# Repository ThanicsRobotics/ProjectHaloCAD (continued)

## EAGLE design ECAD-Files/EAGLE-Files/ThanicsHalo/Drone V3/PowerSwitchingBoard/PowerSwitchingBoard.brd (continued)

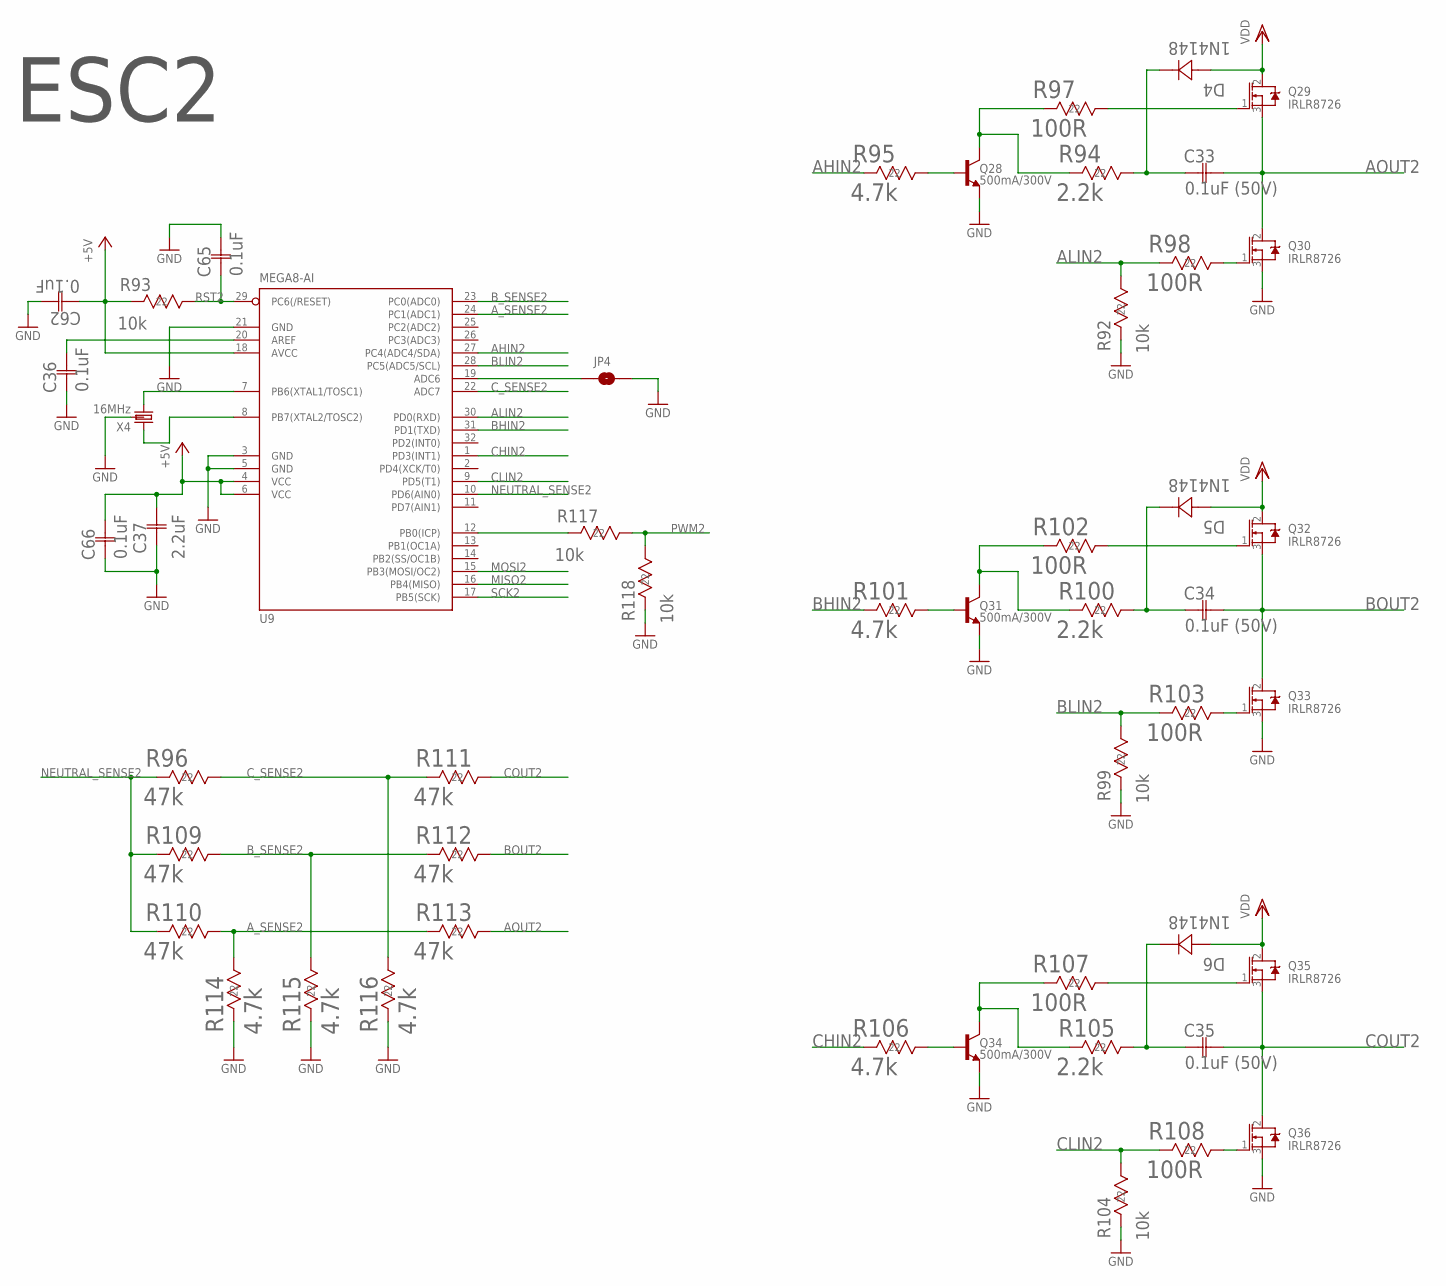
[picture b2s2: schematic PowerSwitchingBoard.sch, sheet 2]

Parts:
C33, C34, C35: 0.1uF (50V); 0402-M
C36, C62, C65, C66: 0.1uF; 0402-M
C37: 2.2uF; G-188-M
D4, D5, D6: 1N4148; SOD123-M
JP4: JUMPER-SMT_2_NO_NO-SILK; SMT-JUMPER_2_NO_NO-SILK
Q28, Q31, Q34: 500mA/300V; SOT23-3
Q29, Q30, Q32, Q33, Q35, Q36: IRLR8726; DPAK
R92, R93, R99, R104, R117, R118: 10k; RC0603N-M
R94, R100, R105: 2.2k; RC0603N-M
R95, R101, R106, R114, R115, R116: 4.7k; RC0603N-M
R96, R109, R110, R111, R112, R113: 47k; RC0603N-M
R97, R98, R102, R103, R107, R108: 100R; RC0603N-M
U9: MEGA8-AI; TQFP32-08
X4: 16MHz; 3-SMD

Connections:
+5V: C37.2 (22), C62.1, C66.2, R93.2 (22), U9.4 (VCC), U9.6 (VCC), U9.18 (AVCC); also elsewhere on the board
AHIN2: R95.2 (22), U9.27 (PC4(ADC4/SDA))
ALIN2: R92.1 (11), R98.2 (22), U9.30 (PD0(RXD))
AOUT2: C33.2, Q29.3 (S), Q30.2 (D), R113.1 (11)
A_SENSE2: R110.1 (11), R113.2 (22), R114.1 (11), U9.24 (PC1(ADC1))
BHIN2: R101.2 (22), U9.31 (PD1(TXD))
BLIN2: R99.1 (11), R103.2 (22), U9.28 (PC5(ADC5/SCL))
BOUT2: C34.2, Q32.3 (S), Q33.2 (D), R112.1 (11)
B_SENSE2: R109.1 (11), R112.2 (22), R115.1 (11), U9.23 (PC0(ADC0))
CHIN2: R106.2 (22), U9.1 (PD3(INT1))
CLIN2: R104.1 (11), R108.2 (22), U9.9 (PD5(T1))
COUT2: C35.2, Q35.3 (S), Q36.2 (D), R111.1 (11)
C_SENSE2: R96.1 (11), R111.2 (22), R116.1 (11), U9.22 (ADC7)
GND: C36.1, C37.1 (11), C62.2, C65.2, C66.1, JP4.2, Q28.2 (E), Q30.3 (S), Q31.2 (E), Q33.3 (S), Q34.2 (E), Q36.3 (S), R92.2 (22), R99.2 (22), R104.2 (22), R114.2 (22), R115.2 (22), R116.2 (22), R118.2 (22), U9.3 (GND), U9.5 (GND), U9.21 (GND), X4.2 (GND); also elsewhere on the board
MISO2: U9.16 (PB4(MISO)); also elsewhere on the board
MOSI2: U9.15 (PB3(MOSI/OC2)); also elsewhere on the board
unnamed: Q28.1 (B), R95.1 (11)
unnamed: Q29.1 (G), R97.1 (11)
unnamed: Q28.3 (C), R94.2 (22), R97.2 (22)
unnamed: C33.1, D4.C (12), R94.1 (11)
unnamed: Q30.1 (G), R98.1 (11)
unnamed: Q31.1 (B), R101.1 (11)
unnamed: Q32.1 (G), R102.1 (11)
unnamed: Q31.3 (C), R100.2 (22), R102.2 (22)
unnamed: C34.1, D5.C (12), R100.1 (11)
unnamed: Q33.1 (G), R103.1 (11)
unnamed: Q34.1 (B), R106.1 (11)
unnamed: Q35.1 (G), R107.1 (11)
unnamed: Q34.3 (C), R105.2 (22), R107.2 (22)
unnamed: C35.1, D6.C (12), R105.1 (11)
unnamed: Q36.1 (G), R108.1 (11)
unnamed: R117.2 (22), U9.12 (PB0(ICP))
unnamed: JP4.1, U9.19 (ADC6)
unnamed: C36.2, U9.20 (AREF)
unnamed: U9.7 (PB6(XTAL1/TOSC1)), X4.3 (2)
unnamed: U9.8 (PB7(XTAL2/TOSC2)), X4.1
NEUTRAL_SENSE2: R96.2 (22), R109.2 (22), R110.2 (22), U9.10 (PD6(AIN0))
PWM2: R117.1 (11), R118.1 (11); also elsewhere on the board
RST2: C65.1, R93.1 (11), U9.29 (PC6(/RESET)); also elsewhere on the board
SCK2: U9.17 (PB5(SCK)); also elsewhere on the board
VDD: D4.A (21), D5.A (21), D6.A (21), Q29.2 (D), Q32.2 (D), Q35.2 (D); also elsewhere on the board

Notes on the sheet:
ESC2

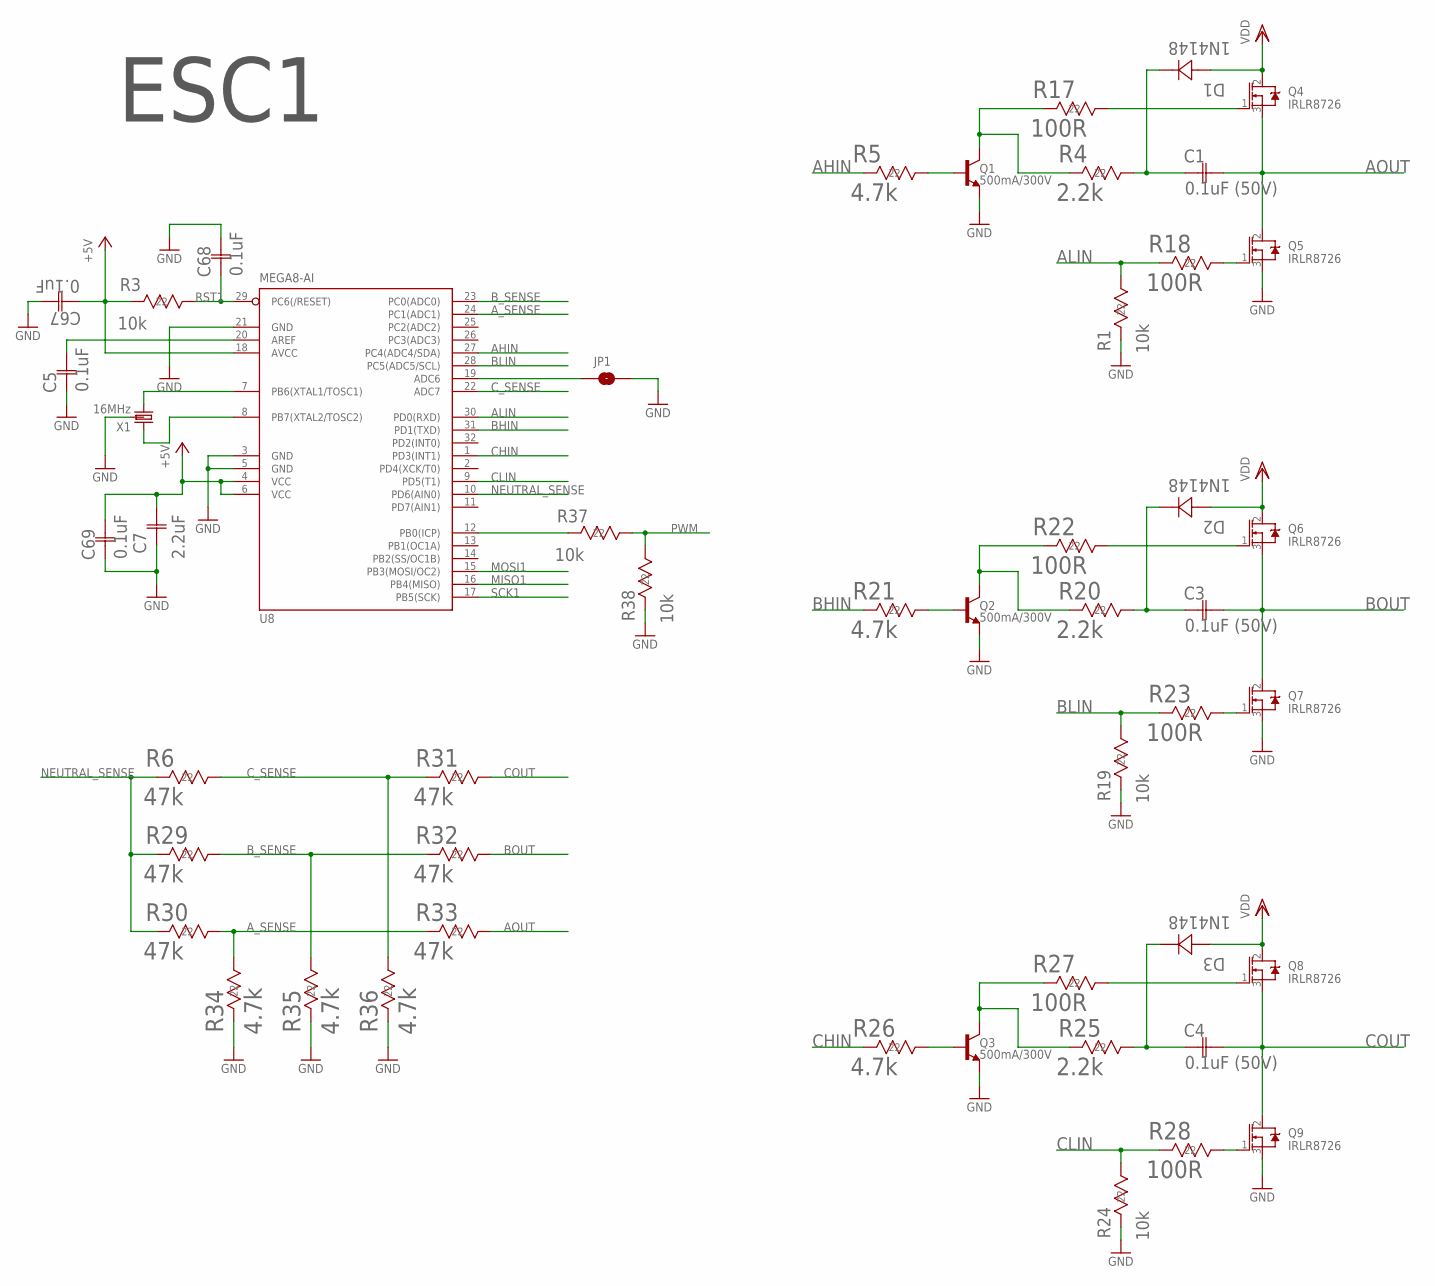
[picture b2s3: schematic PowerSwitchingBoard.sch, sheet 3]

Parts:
C1, C3, C4: 0.1uF (50V); 0402-M
C5, C67, C68, C69: 0.1uF; 0402-M
C7: 2.2uF; G-188-M
D1, D2, D3: 1N4148; SOD123-M
JP1: JUMPER-SMT_2_NO_NO-SILK; SMT-JUMPER_2_NO_NO-SILK
Q1, Q2, Q3: 500mA/300V; SOT23-3
Q4, Q5, Q6, Q7, Q8, Q9: IRLR8726; DPAK
R1, R3, R19, R24, R37, R38: 10k; RC0603N-M
R4, R20, R25: 2.2k; RC0603N-M
R5, R21, R26, R34, R35, R36: 4.7k; RC0603N-M
R6, R29, R30, R31, R32, R33: 47k; RC0603N-M
R17, R18, R22, R23, R27, R28: 100R; RC0603N-M
U8: MEGA8-AI; TQFP32-08
X1: 16MHz; 3-SMD

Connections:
+5V: C7.2 (22), C67.1, C69.2, R3.2 (22), U8.4 (VCC), U8.6 (VCC), U8.18 (AVCC); also elsewhere on the board
AHIN: R5.2 (22), U8.27 (PC4(ADC4/SDA))
ALIN: R1.1 (11), R18.2 (22), U8.30 (PD0(RXD))
AOUT: C1.2, Q4.3 (S), Q5.2 (D), R33.1 (11)
A_SENSE: R30.1 (11), R33.2 (22), R34.1 (11), U8.24 (PC1(ADC1))
BHIN: R21.2 (22), U8.31 (PD1(TXD))
BLIN: R19.1 (11), R23.2 (22), U8.28 (PC5(ADC5/SCL))
BOUT: C3.2, Q6.3 (S), Q7.2 (D), R32.1 (11)
B_SENSE: R29.1 (11), R32.2 (22), R35.1 (11), U8.23 (PC0(ADC0))
CHIN: R26.2 (22), U8.1 (PD3(INT1))
CLIN: R24.1 (11), R28.2 (22), U8.9 (PD5(T1))
COUT: C4.2, Q8.3 (S), Q9.2 (D), R31.1 (11)
C_SENSE: R6.1 (11), R31.2 (22), R36.1 (11), U8.22 (ADC7)
GND: C5.1, C7.1 (11), C67.2, C68.2, C69.1, JP1.2, Q1.2 (E), Q2.2 (E), Q3.2 (E), Q5.3 (S), Q7.3 (S), Q9.3 (S), R1.2 (22), R19.2 (22), R24.2 (22), R34.2 (22), R35.2 (22), R36.2 (22), R38.2 (22), U8.3 (GND), U8.5 (GND), U8.21 (GND), X1.2 (GND); also elsewhere on the board
MISO1: U8.16 (PB4(MISO)); also elsewhere on the board
MOSI1: U8.15 (PB3(MOSI/OC2)); also elsewhere on the board
unnamed: Q1.1 (B), R5.1 (11)
unnamed: Q4.1 (G), R17.1 (11)
unnamed: Q1.3 (C), R4.2 (22), R17.2 (22)
unnamed: Q2.1 (B), R21.1 (11)
unnamed: C1.1, D1.C (12), R4.1 (11)
unnamed: Q5.1 (G), R18.1 (11)
unnamed: Q6.1 (G), R22.1 (11)
unnamed: Q2.3 (C), R20.2 (22), R22.2 (22)
unnamed: C3.1, D2.C (12), R20.1 (11)
unnamed: Q7.1 (G), R23.1 (11)
unnamed: Q3.1 (B), R26.1 (11)
unnamed: Q8.1 (G), R27.1 (11)
unnamed: Q3.3 (C), R25.2 (22), R27.2 (22)
unnamed: C4.1, D3.C (12), R25.1 (11)
unnamed: Q9.1 (G), R28.1 (11)
unnamed: C5.2, U8.20 (AREF)
unnamed: U8.7 (PB6(XTAL1/TOSC1)), X1.3 (2)
unnamed: U8.8 (PB7(XTAL2/TOSC2)), X1.1
unnamed: JP1.1, U8.19 (ADC6)
unnamed: R37.2 (22), U8.12 (PB0(ICP))
NEUTRAL_SENSE: R6.2 (22), R29.2 (22), R30.2 (22), U8.10 (PD6(AIN0))
PWM: R37.1 (11), R38.1 (11); also elsewhere on the board
RST1: C68.1, R3.1 (11), U8.29 (PC6(/RESET)); also elsewhere on the board
SCK1: U8.17 (PB5(SCK)); also elsewhere on the board
VDD: D1.A (21), D2.A (21), D3.A (21), Q4.2 (D), Q6.2 (D), Q8.2 (D); also elsewhere on the board

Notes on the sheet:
ESC1

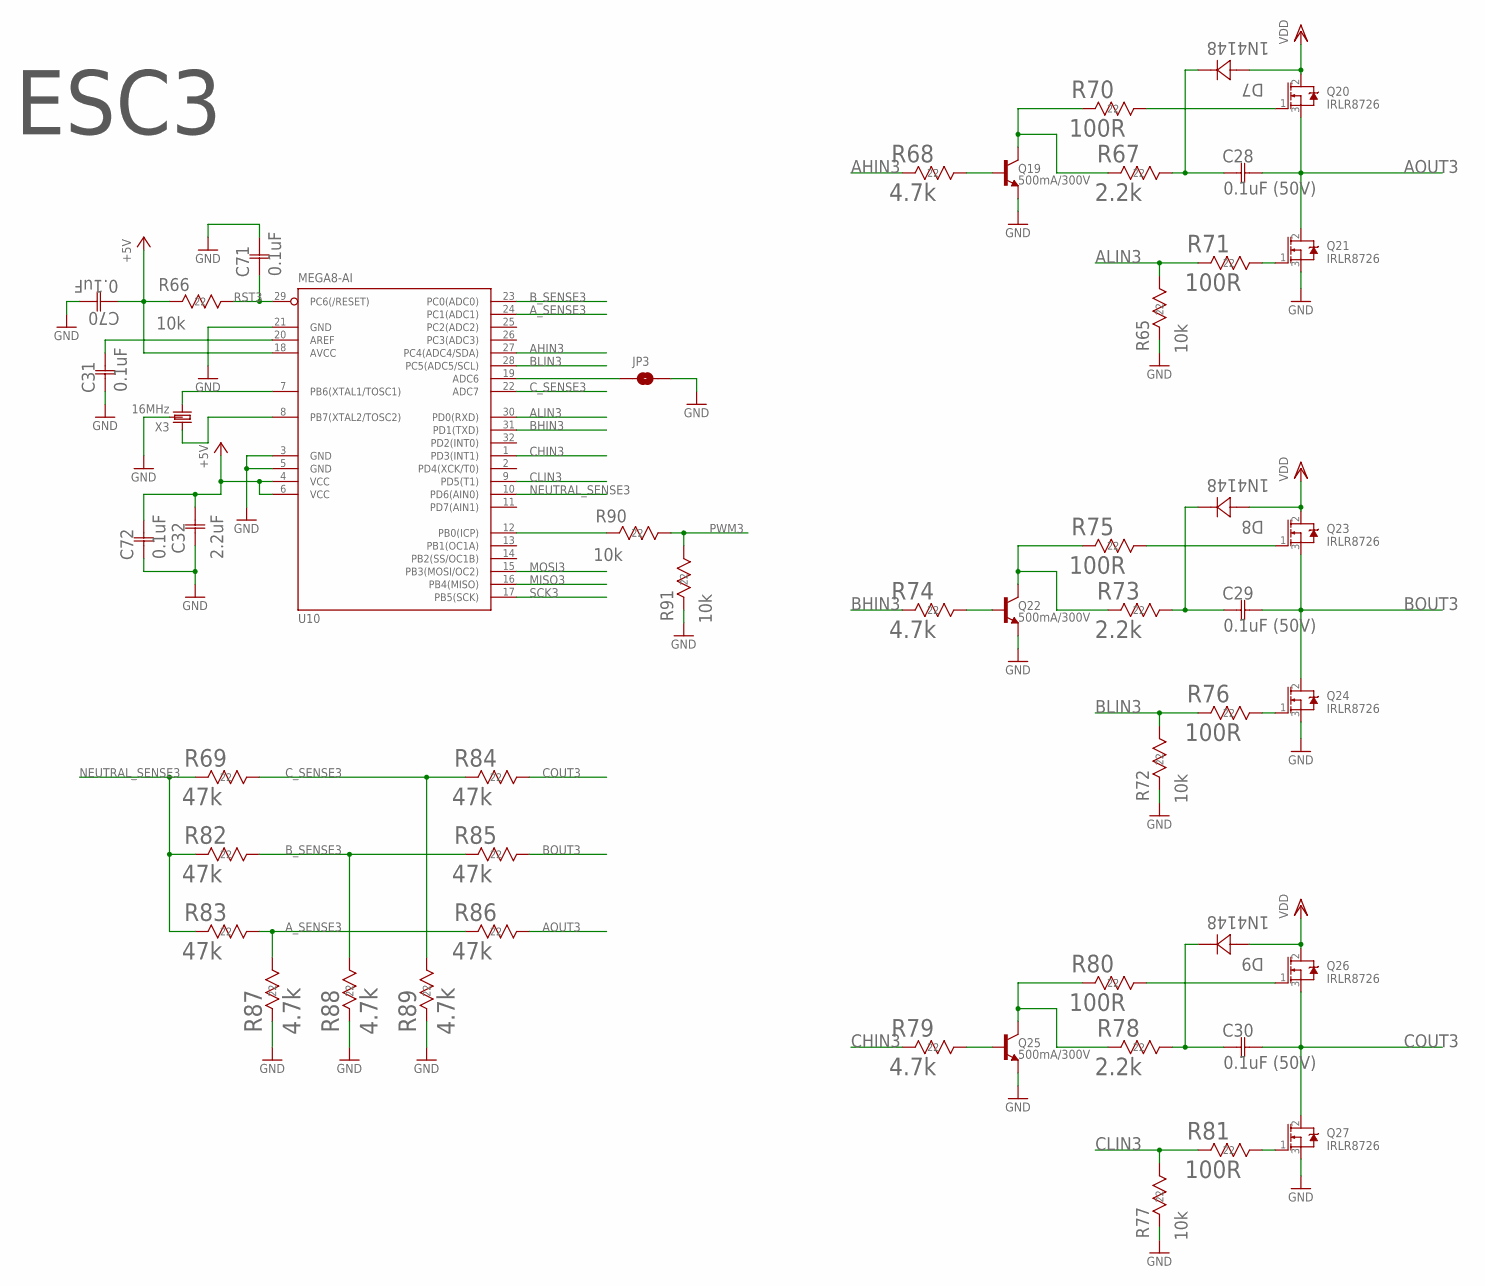
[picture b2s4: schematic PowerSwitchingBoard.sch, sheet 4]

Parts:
C28, C29, C30: 0.1uF (50V); 0402-M
C31, C70, C71, C72: 0.1uF; 0402-M
C32: 2.2uF; G-188-M
D7, D8, D9: 1N4148; SOD123-M
JP3: JUMPER-SMT_2_NO_NO-SILK; SMT-JUMPER_2_NO_NO-SILK
Q19, Q22, Q25: 500mA/300V; SOT23-3
Q20, Q21, Q23, Q24, Q26, Q27: IRLR8726; DPAK
R65, R66, R72, R77, R90, R91: 10k; RC0603N-M
R67, R73, R78: 2.2k; RC0603N-M
R68, R74, R79, R87, R88, R89: 4.7k; RC0603N-M
R69, R82, R83, R84, R85, R86: 47k; RC0603N-M
R70, R71, R75, R76, R80, R81: 100R; RC0603N-M
U10: MEGA8-AI; TQFP32-08
X3: 16MHz; 3-SMD

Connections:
+5V: C32.2 (22), C70.1, C72.2, R66.2 (22), U10.4 (VCC), U10.6 (VCC), U10.18 (AVCC); also elsewhere on the board
AHIN3: R68.2 (22), U10.27 (PC4(ADC4/SDA))
ALIN3: R65.1 (11), R71.2 (22), U10.30 (PD0(RXD))
AOUT3: C28.2, Q20.3 (S), Q21.2 (D), R86.1 (11)
A_SENSE3: R83.1 (11), R86.2 (22), R87.1 (11), U10.24 (PC1(ADC1))
BHIN3: R74.2 (22), U10.31 (PD1(TXD))
BLIN3: R72.1 (11), R76.2 (22), U10.28 (PC5(ADC5/SCL))
BOUT3: C29.2, Q23.3 (S), Q24.2 (D), R85.1 (11)
B_SENSE3: R82.1 (11), R85.2 (22), R88.1 (11), U10.23 (PC0(ADC0))
CHIN3: R79.2 (22), U10.1 (PD3(INT1))
CLIN3: R77.1 (11), R81.2 (22), U10.9 (PD5(T1))
COUT3: C30.2, Q26.3 (S), Q27.2 (D), R84.1 (11)
C_SENSE3: R69.1 (11), R84.2 (22), R89.1 (11), U10.22 (ADC7)
GND: C31.1, C32.1 (11), C70.2, C71.2, C72.1, JP3.2, Q19.2 (E), Q21.3 (S), Q22.2 (E), Q24.3 (S), Q25.2 (E), Q27.3 (S), R65.2 (22), R72.2 (22), R77.2 (22), R87.2 (22), R88.2 (22), R89.2 (22), R91.2 (22), U10.3 (GND), U10.5 (GND), U10.21 (GND), X3.2 (GND); also elsewhere on the board
MISO3: U10.16 (PB4(MISO)); also elsewhere on the board
MOSI3: U10.15 (PB3(MOSI/OC2)); also elsewhere on the board
unnamed: Q19.1 (B), R68.1 (11)
unnamed: Q20.1 (G), R70.1 (11)
unnamed: Q19.3 (C), R67.2 (22), R70.2 (22)
unnamed: C28.1, D7.C (12), R67.1 (11)
unnamed: Q21.1 (G), R71.1 (11)
unnamed: Q22.1 (B), R74.1 (11)
unnamed: Q23.1 (G), R75.1 (11)
unnamed: Q22.3 (C), R73.2 (22), R75.2 (22)
unnamed: C29.1, D8.C (12), R73.1 (11)
unnamed: Q24.1 (G), R76.1 (11)
unnamed: Q25.1 (B), R79.1 (11)
unnamed: Q26.1 (G), R80.1 (11)
unnamed: Q25.3 (C), R78.2 (22), R80.2 (22)
unnamed: C30.1, D9.C (12), R78.1 (11)
unnamed: Q27.1 (G), R81.1 (11)
unnamed: R90.2 (22), U10.12 (PB0(ICP))
unnamed: JP3.1, U10.19 (ADC6)
unnamed: C31.2, U10.20 (AREF)
unnamed: U10.7 (PB6(XTAL1/TOSC1)), X3.3 (2)
unnamed: U10.8 (PB7(XTAL2/TOSC2)), X3.1
NEUTRAL_SENSE3: R69.2 (22), R82.2 (22), R83.2 (22), U10.10 (PD6(AIN0))
PWM3: R90.1 (11), R91.1 (11); also elsewhere on the board
RST3: C71.1, R66.1 (11), U10.29 (PC6(/RESET)); also elsewhere on the board
SCK3: U10.17 (PB5(SCK)); also elsewhere on the board
VDD: D7.A (21), D8.A (21), D9.A (21), Q20.2 (D), Q23.2 (D), Q26.2 (D); also elsewhere on the board

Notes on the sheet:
ESC3

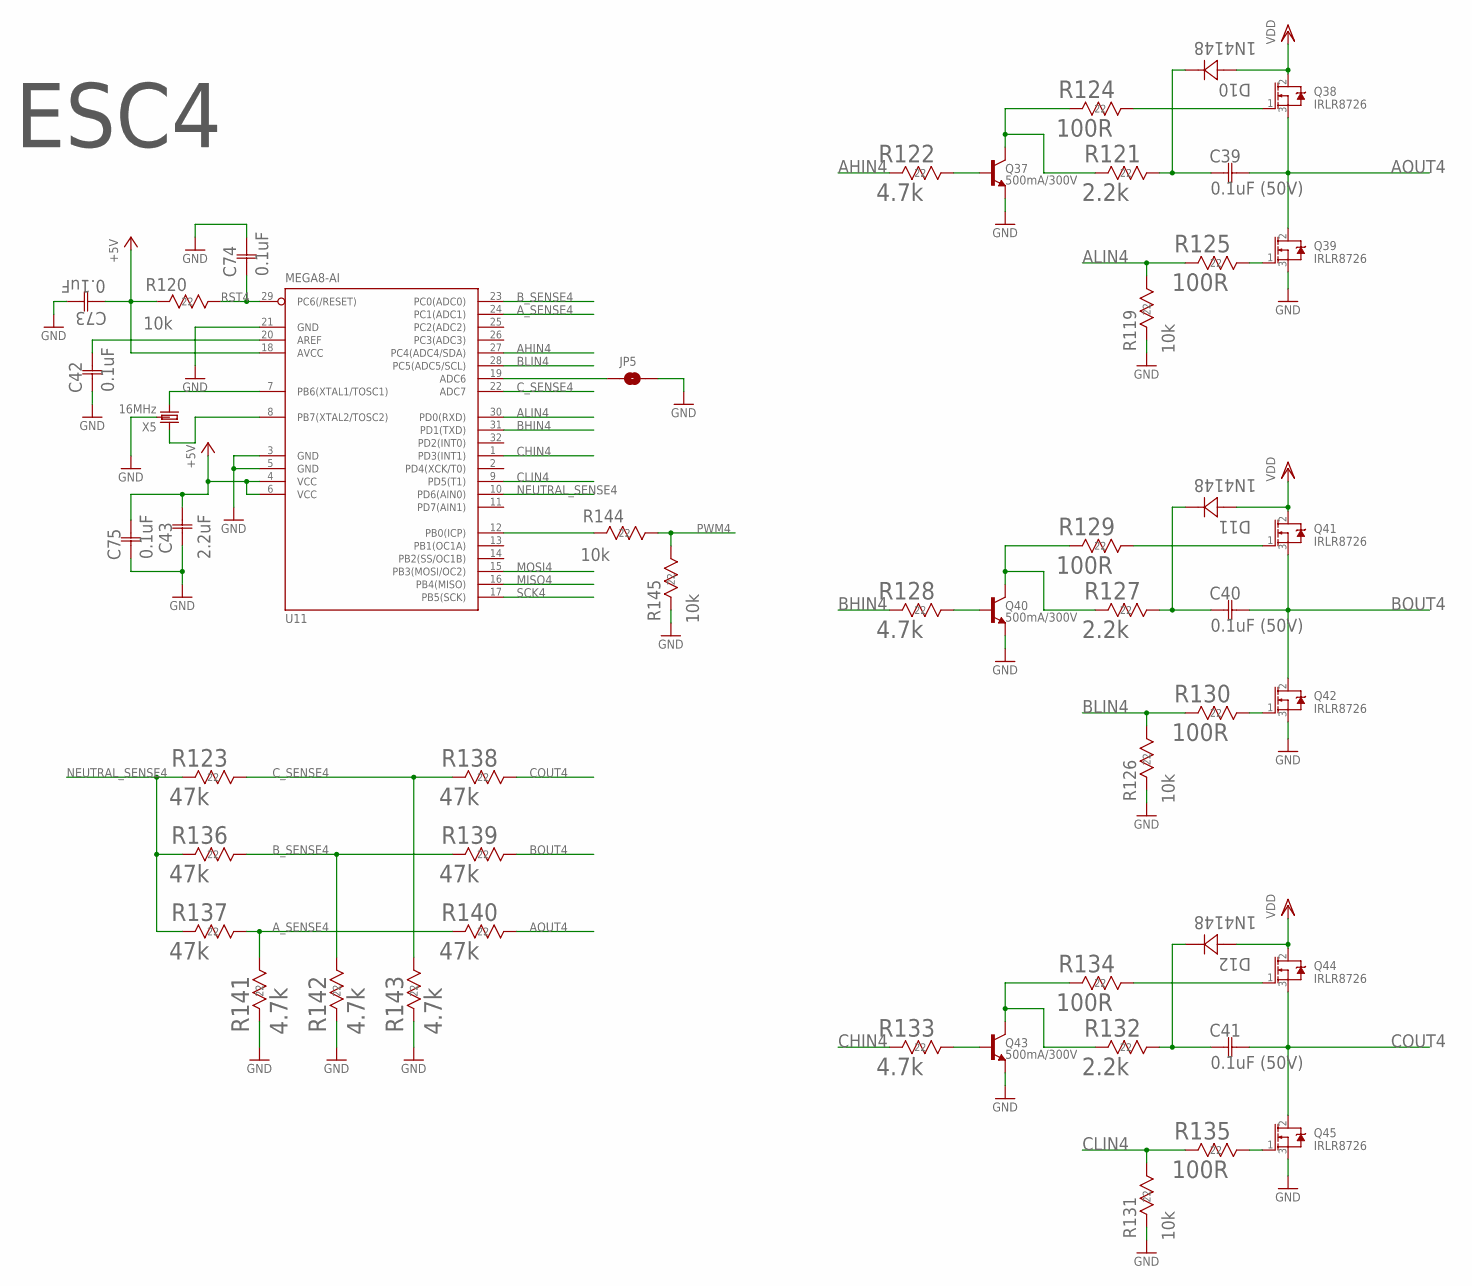
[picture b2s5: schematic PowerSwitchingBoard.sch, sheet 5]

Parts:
C39, C40, C41: 0.1uF (50V); 0402-M
C42, C73, C74, C75: 0.1uF; 0402-M
C43: 2.2uF; G-188-M
D10, D11, D12: 1N4148; SOD123-M
JP5: JUMPER-SMT_2_NO_NO-SILK; SMT-JUMPER_2_NO_NO-SILK
Q37, Q40, Q43: 500mA/300V; SOT23-3
Q38, Q39, Q41, Q42, Q44, Q45: IRLR8726; DPAK
R119, R120, R126, R131, R144, R145: 10k; RC0603N-M
R121, R127, R132: 2.2k; RC0603N-M
R122, R128, R133, R141, R142, R143: 4.7k; RC0603N-M
R123, R136, R137, R138, R139, R140: 47k; RC0603N-M
R124, R125, R129, R130, R134, R135: 100R; RC0603N-M
U11: MEGA8-AI; TQFP32-08
X5: 16MHz; 3-SMD

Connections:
+5V: C43.2 (22), C73.1, C75.2, R120.2 (22), U11.4 (VCC), U11.6 (VCC), U11.18 (AVCC); also elsewhere on the board
AHIN4: R122.2 (22), U11.27 (PC4(ADC4/SDA))
ALIN4: R119.1 (11), R125.2 (22), U11.30 (PD0(RXD))
AOUT4: C39.2, Q38.3 (S), Q39.2 (D), R140.1 (11)
A_SENSE4: R137.1 (11), R140.2 (22), R141.1 (11), U11.24 (PC1(ADC1))
BHIN4: R128.2 (22), U11.31 (PD1(TXD))
BLIN4: R126.1 (11), R130.2 (22), U11.28 (PC5(ADC5/SCL))
BOUT4: C40.2, Q41.3 (S), Q42.2 (D), R139.1 (11)
B_SENSE4: R136.1 (11), R139.2 (22), R142.1 (11), U11.23 (PC0(ADC0))
CHIN4: R133.2 (22), U11.1 (PD3(INT1))
CLIN4: R131.1 (11), R135.2 (22), U11.9 (PD5(T1))
COUT4: C41.2, Q44.3 (S), Q45.2 (D), R138.1 (11)
C_SENSE4: R123.1 (11), R138.2 (22), R143.1 (11), U11.22 (ADC7)
GND: C42.1, C43.1 (11), C73.2, C74.2, C75.1, JP5.2, Q37.2 (E), Q39.3 (S), Q40.2 (E), Q42.3 (S), Q43.2 (E), Q45.3 (S), R119.2 (22), R126.2 (22), R131.2 (22), R141.2 (22), R142.2 (22), R143.2 (22), R145.2 (22), U11.3 (GND), U11.5 (GND), U11.21 (GND), X5.2 (GND); also elsewhere on the board
MISO4: U11.16 (PB4(MISO)); also elsewhere on the board
MOSI4: U11.15 (PB3(MOSI/OC2)); also elsewhere on the board
unnamed: Q37.1 (B), R122.1 (11)
unnamed: Q38.1 (G), R124.1 (11)
unnamed: Q37.3 (C), R121.2 (22), R124.2 (22)
unnamed: C39.1, D10.C (12), R121.1 (11)
unnamed: Q39.1 (G), R125.1 (11)
unnamed: Q40.1 (B), R128.1 (11)
unnamed: Q41.1 (G), R129.1 (11)
unnamed: Q40.3 (C), R127.2 (22), R129.2 (22)
unnamed: C40.1, D11.C (12), R127.1 (11)
unnamed: Q42.1 (G), R130.1 (11)
unnamed: Q43.1 (B), R133.1 (11)
unnamed: Q44.1 (G), R134.1 (11)
unnamed: Q43.3 (C), R132.2 (22), R134.2 (22)
unnamed: C41.1, D12.C (12), R132.1 (11)
unnamed: Q45.1 (G), R135.1 (11)
unnamed: R144.2 (22), U11.12 (PB0(ICP))
unnamed: JP5.1, U11.19 (ADC6)
unnamed: C42.2, U11.20 (AREF)
unnamed: U11.7 (PB6(XTAL1/TOSC1)), X5.3 (2)
unnamed: U11.8 (PB7(XTAL2/TOSC2)), X5.1
NEUTRAL_SENSE4: R123.2 (22), R136.2 (22), R137.2 (22), U11.10 (PD6(AIN0))
PWM4: R144.1 (11), R145.1 (11); also elsewhere on the board
RST4: C74.1, R120.1 (11), U11.29 (PC6(/RESET)); also elsewhere on the board
SCK4: U11.17 (PB5(SCK)); also elsewhere on the board
VDD: D10.A (21), D11.A (21), D12.A (21), Q38.2 (D), Q41.2 (D), Q44.2 (D); also elsewhere on the board

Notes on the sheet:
ESC4

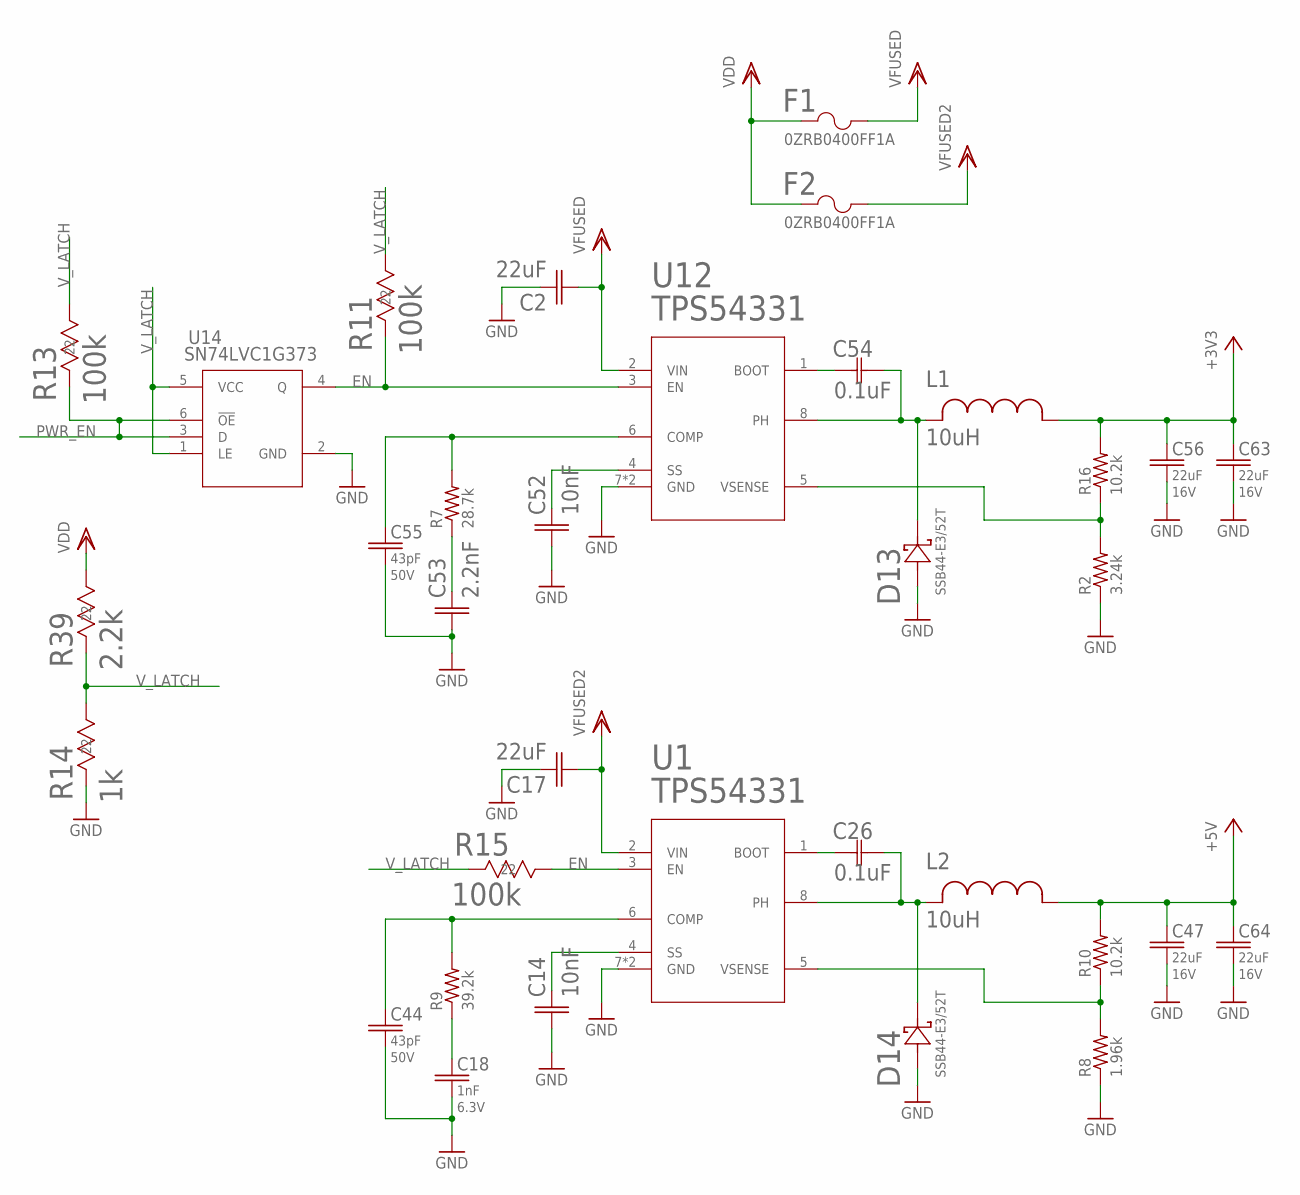
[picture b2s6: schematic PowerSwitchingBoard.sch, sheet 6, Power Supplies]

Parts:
C2, C17: 22uF; 1210_CAPACITOR
C14, C52: 10nF; 0603_CAPACITOR
C18: 1nF; C0402
C26, C54: 0.1uF; 0402-M
C44, C55: 43pF; C0603
C47, C56, C63, C64: 22uF; C0805
C53: 2.2nF; 0402_CAPACITOR
D13, D14: SSB44-E3/52T; DIODE_DO214AA_MBRS-M
F1, F2: 0ZRB0400FF1A
L1, L2: 10uH; PA431.XXX
R2: 3.24k; R0603
R7: 28.7k; R0402
R8: 1.96k; R0603
R9: 39.2k; R0402
R10, R16: 10.2k; R0402
R11, R13, R15: 100k; RC0603N-M
R14: 1k; RC0603N-M
R39: 2.2k; RC0603N-M
U1, U12: TPS54331DRD8-M; D8-M
U14: SN74LVC1G373DCKRDCK6-M; DCK6-M

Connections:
+3V3: C56.1, C63.1, L1.P$2 (2), R16.2; also elsewhere on the board
+5V: C47.1, C64.1, L2.P$2 (2), R10.2; also elsewhere on the board
EN: R11.2 (22), R15.1 (11), U1.3 (EN), U12.3 (EN), U14.4 (Q)
GND: C2.2, C14.1, C17.2, C18.2, C44.2, C47.2, C52.1, C53.1, C55.2, C56.2, C63.2, C64.2, D13.2 (21), D14.2 (21), R2.1, R8.1, R14.2 (22), U1.7 (GND), U1.EP (GND), U12.7 (GND), U12.EP (GND), U14.2 (GND); also elsewhere on the board
unnamed: C55.1, R7.2, U12.6 (COMP)
unnamed: C53.2, R7.1
unnamed: C52.2, U12.4 (SS)
unnamed: C54.1, U12.1 (BOOT)
unnamed: C44.1, R9.2, U1.6 (COMP)
unnamed: C18.1, R9.1
unnamed: C14.2, U1.4 (SS)
unnamed: C26.1, U1.1 (BOOT)
unnamed: C26.2, D14.1 (12), L2.P$1 (1), U1.8 (PH)
unnamed: C54.2, D13.1 (12), L1.P$1 (1), U12.8 (PH)
unnamed: R8.2, R10.1, U1.5 (VSENSE)
unnamed: R2.2, R16.1, U12.5 (VSENSE)
PWR_EN: R13.2 (22), U14.3 (D), U14.6 (!OE); also elsewhere on the board
V2FUSED: C17.1, F2.2, U1.2 (VIN)
VDD: F1.1, F2.1, R39.1 (11); also elsewhere on the board
VFUSED: C2.1, F1.2, U12.2 (VIN)
V_LATCH: R11.1 (11), R13.1 (11), R14.1 (11), R15.2 (22), R39.2 (22), U14.1 (LE), U14.5 (VCC)

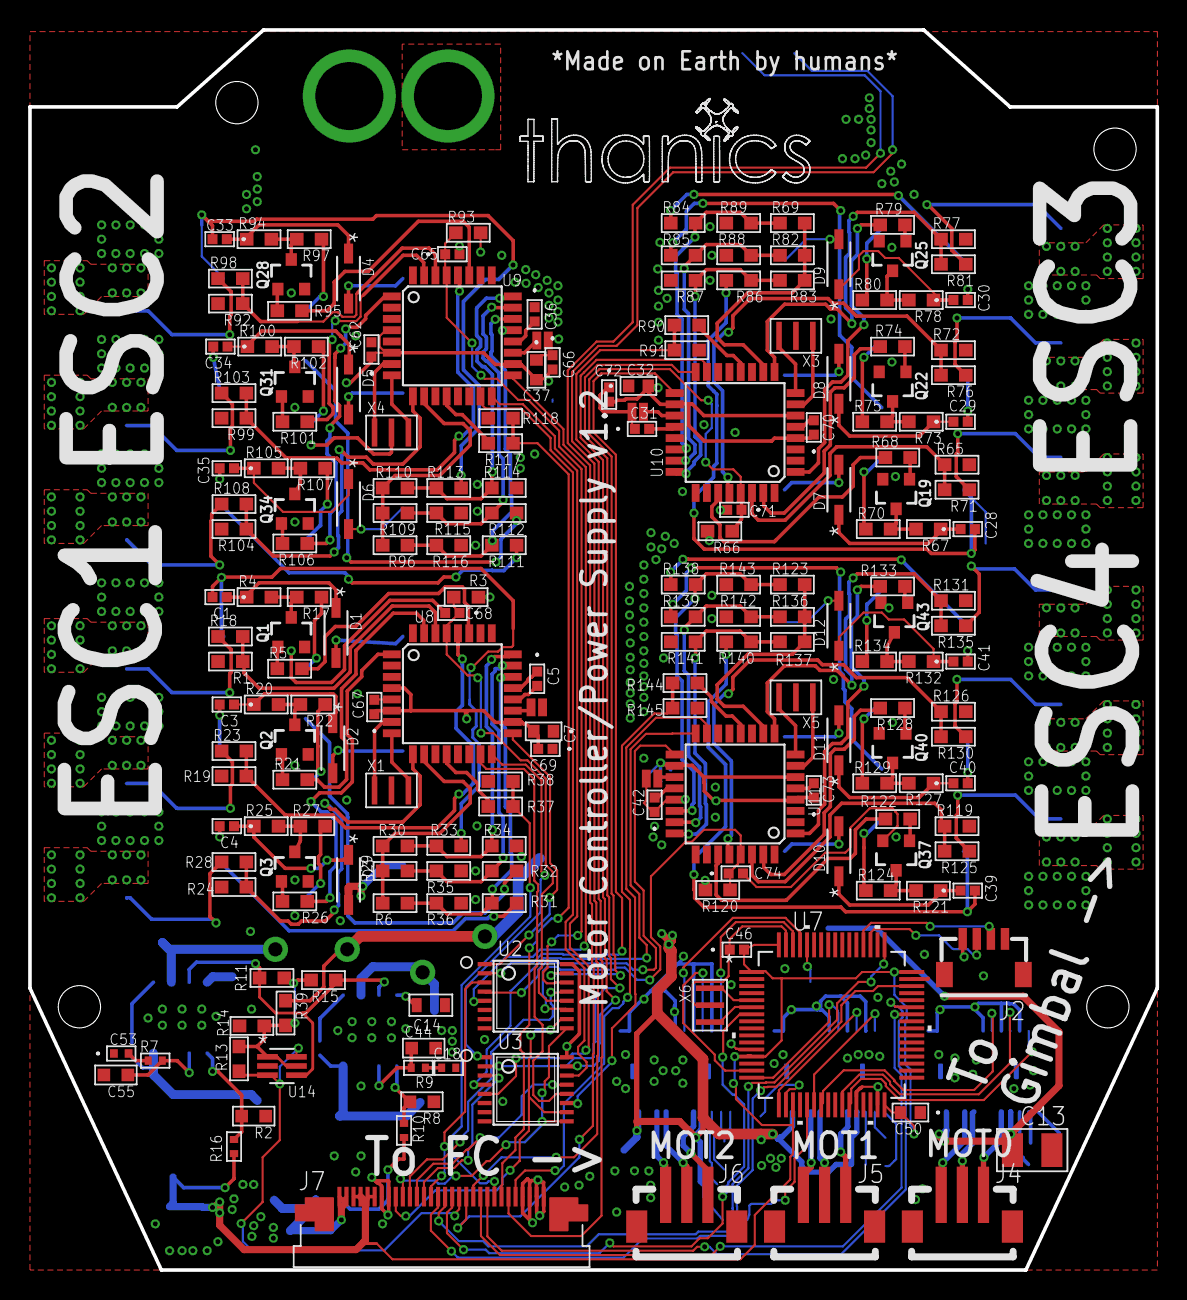
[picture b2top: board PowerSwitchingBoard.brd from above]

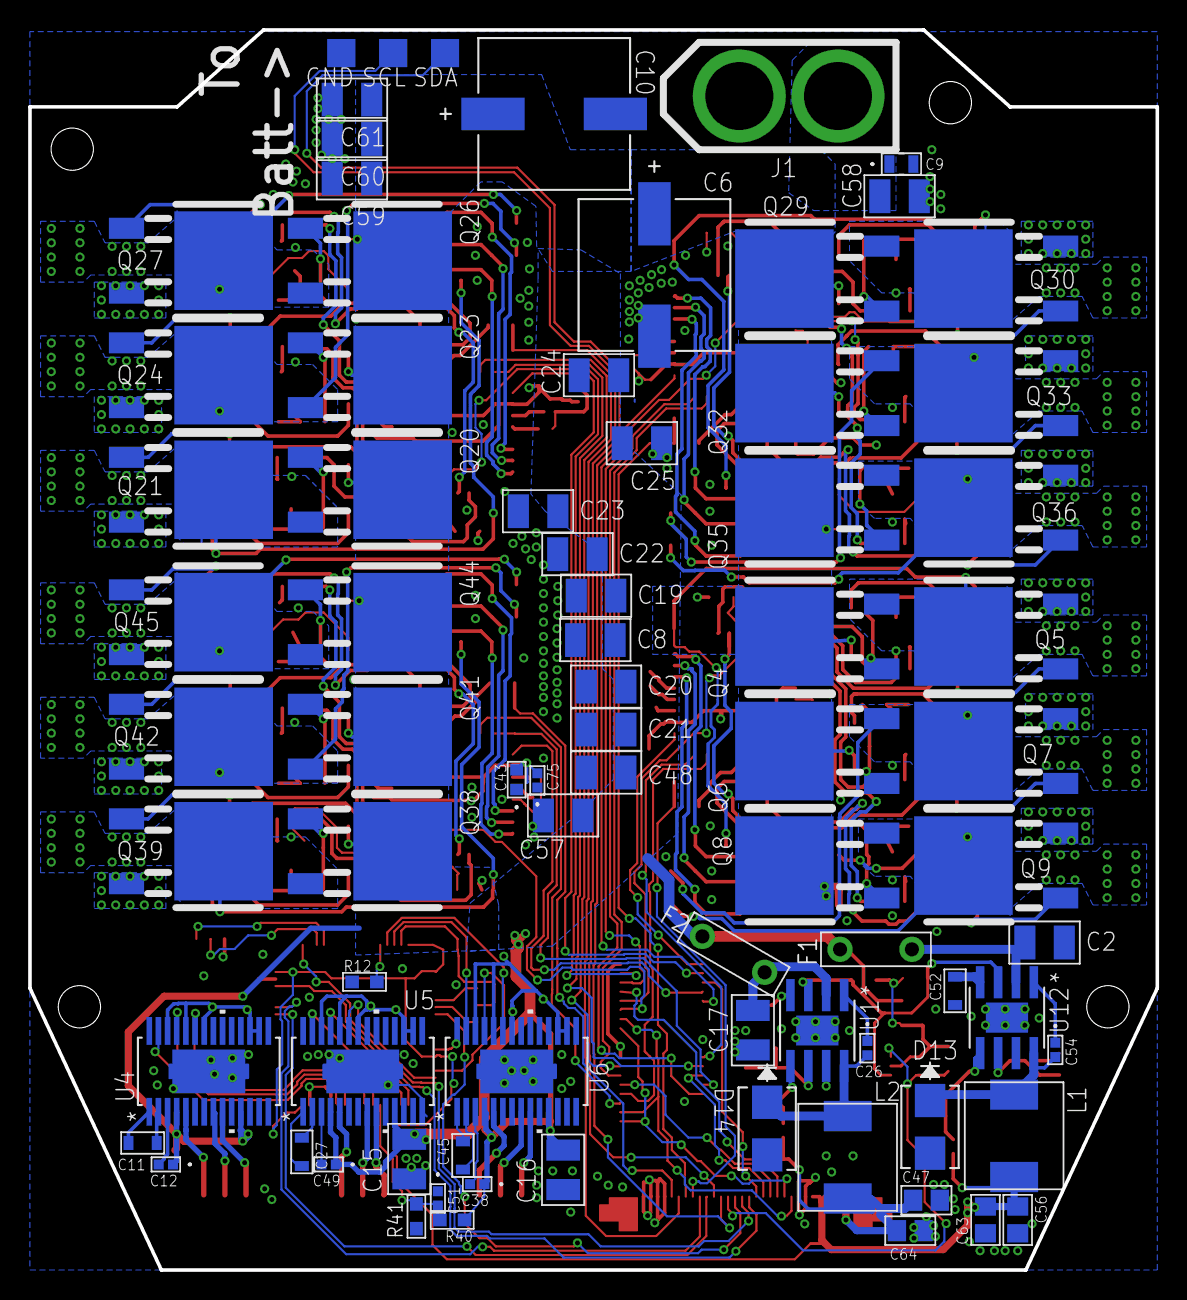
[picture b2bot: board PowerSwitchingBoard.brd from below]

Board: 4 copper layers, 80.0 x 88.0 mm, 282 parts (79 on the bottom side), 219 nets.
